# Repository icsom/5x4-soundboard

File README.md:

# 5x4-soundboard
DFPlayer Mini &amp; atmega328p based soundboard with 20 buttons

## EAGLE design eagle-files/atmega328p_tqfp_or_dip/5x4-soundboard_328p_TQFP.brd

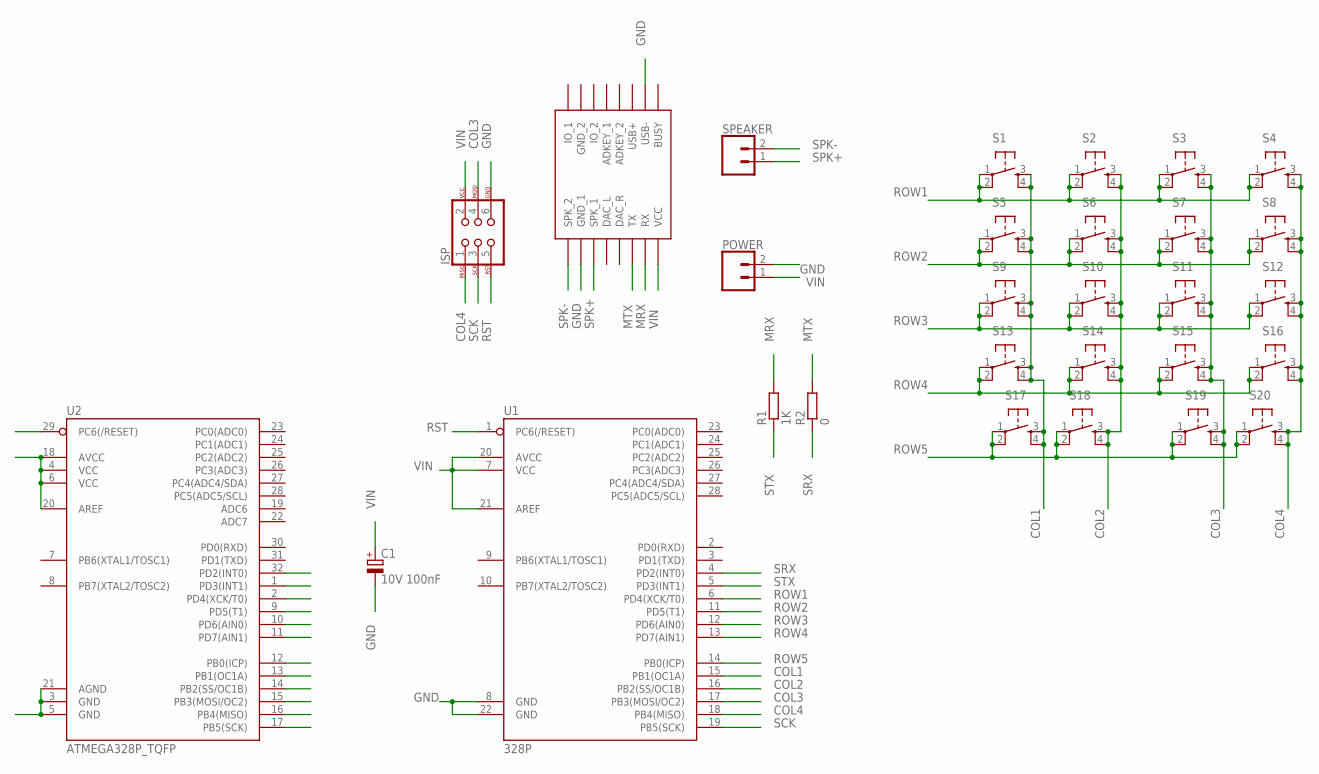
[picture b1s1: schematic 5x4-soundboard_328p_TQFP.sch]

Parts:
C1: 10V 100nF; E5-6
ISP: AVR_SPI_PROG_3X2PTH; 2X3
POWER: CONN_02LOCK_LONGPADS; 1X02_LOCK_LONGPADS
R1: 1K; 0207/10
R2: 0; 0207/10
S1, S2, S3, S4, S5, S6, S7, S8, S9, S10, S11, S12, S13, S14, S15, S16, S17, S18, S19, S20: TAC_SWITCHPTH; TACTILE-PTH
SPEAKER: CONN_02LOCK_LONGPADS; 1X02_LOCK_LONGPADS
U1: 328P; DIP28
U2: ATMEGA328P_TQFP; TQFP32-08
U$1: DFPLAYER

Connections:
COL1: S1.3, S1.4, S5.3, S5.4, S9.3, S9.4, S13.3, S13.4, S17.3, S17.4, U1.15 (PB1(OC1A)), U2.13 (PB1(OC1A))
COL2: S2.3, S2.4, S6.3, S6.4, S10.3, S10.4, S14.3, S14.4, S18.3, S18.4, U1.16 (PB2(SS/OC1B)), U2.14 (PB2(SS/OC1B))
COL3: ISP.4, S3.3, S3.4, S7.3, S7.4, S11.3, S11.4, S15.3, S15.4, S19.3, S19.4, U1.17 (PB3(MOSI/OC2)), U2.15 (PB3(MOSI/OC2))
COL4: ISP.1, S4.3, S4.4, S8.3, S8.4, S12.3, S12.4, S16.3, S16.4, S20.3, S20.4, U1.18 (PB4(MISO)), U2.16 (PB4(MISO))
GND: C1.-, ISP.6, POWER.2, U1.8 (GND), U1.22 (GND), U2.3 (GND), U2.5 (GND), U2.21 (AGND), U$1.GND_1, U$1.USB-
MRX: R1.2, U$1.RX
MTX: R2.2, U$1.TX
ROW1: S1.1, S1.2, S2.1, S2.2, S3.1, S3.2, S4.1, S4.2, U1.6 (PD4(XCK/T0)), U2.2 (PD4(XCK/T0))
ROW2: S5.1, S5.2, S6.1, S6.2, S7.1, S7.2, S8.1, S8.2, U1.11 (PD5(T1)), U2.9 (PD5(T1))
ROW3: S9.1, S9.2, S10.1, S10.2, S11.1, S11.2, S12.1, S12.2, U1.12 (PD6(AIN0)), U2.10 (PD6(AIN0))
ROW4: S13.1, S13.2, S14.1, S14.2, S15.1, S15.2, S16.1, S16.2, U1.13 (PD7(AIN1)), U2.11 (PD7(AIN1))
ROW5: S17.1, S17.2, S18.1, S18.2, S19.1, S19.2, S20.1, S20.2, U1.14 (PB0(ICP)), U2.12 (PB0(ICP))
RST: ISP.5, U1.1 (PC6(/RESET)), U2.29 (PC6(/RESET))
SCK: ISP.3, U1.19 (PB5(SCK)), U2.17 (PB5(SCK))
SPK+: SPEAKER.1, U$1.SPK1 (SPK_1)
SPK-: SPEAKER.2, U$1.SPK2 (SPK_2)
SRX: R2.1, U1.4 (PD2(INT0)), U2.32 (PD2(INT0))
STX: R1.1, U1.5 (PD3(INT1)), U2.1 (PD3(INT1))
VIN: C1.+, ISP.2, POWER.1, U1.7 (VCC), U1.20 (AVCC), U1.21 (AREF), U2.4 (VCC), U2.6 (VCC), U2.18 (AVCC), U2.20 (AREF), U$1.VCC

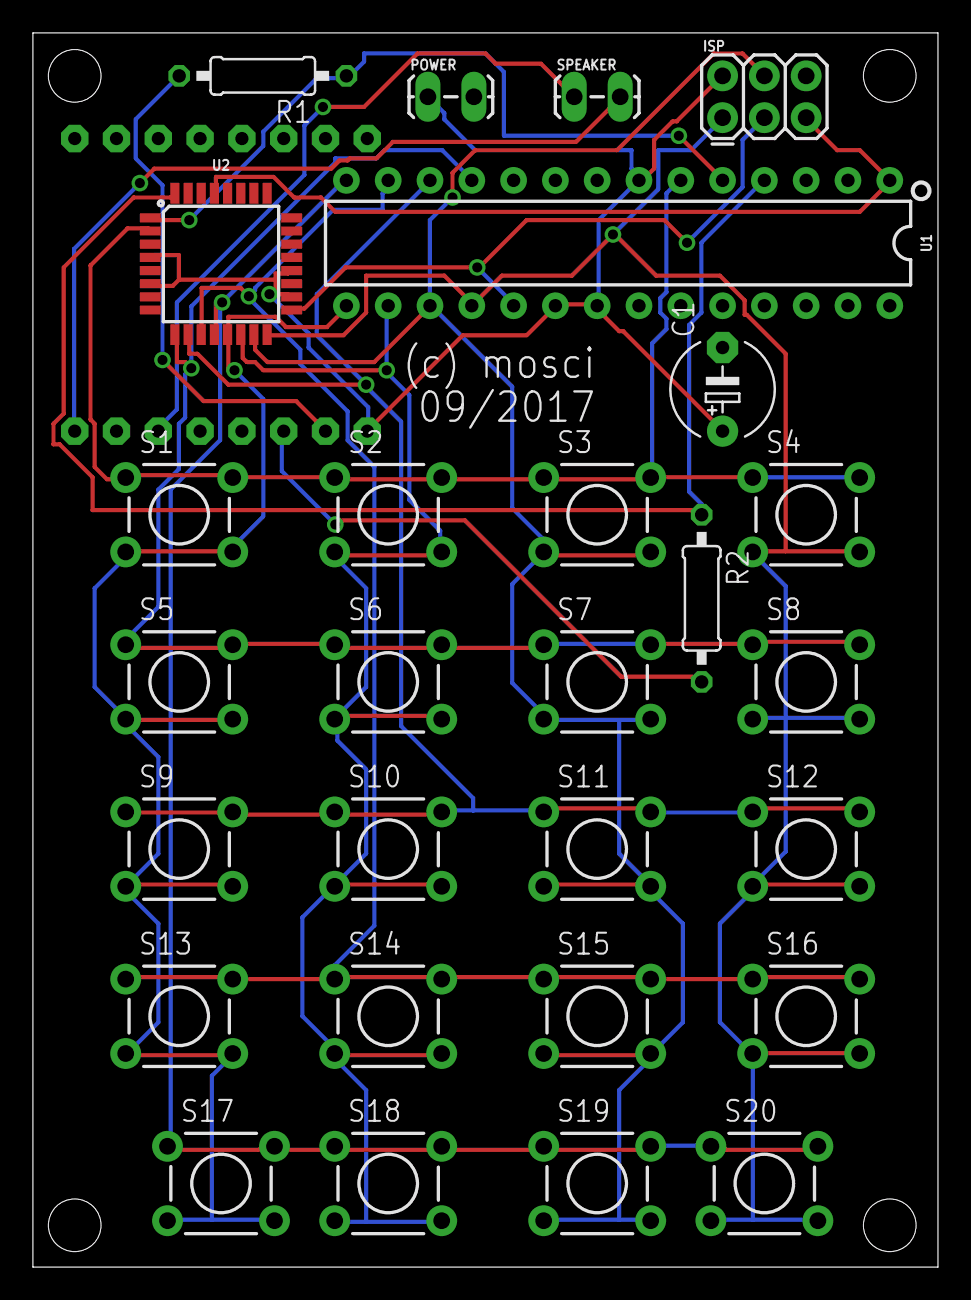
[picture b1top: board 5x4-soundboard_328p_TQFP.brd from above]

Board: 2 copper layers, 55.0 x 75.0 mm, 29 parts (1 on the bottom side), 19 nets.

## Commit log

2017-10-14 added eagle-schematic as picture
2017-10-14 pictures of prototypes
2017-10-15 added compiled hex, arduino-ide-project and 8 MHz bootloader
2017-10-15 renamed avrdude_help
2017-10-15 added eagle-files for atmega328p tqfp

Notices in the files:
parts and their libraries:
SparkFun-Connectors: Licensing: Creative Commons ShareAlike 4.0 International - https://creativecommons.org/licenses/by-sa/4.0
